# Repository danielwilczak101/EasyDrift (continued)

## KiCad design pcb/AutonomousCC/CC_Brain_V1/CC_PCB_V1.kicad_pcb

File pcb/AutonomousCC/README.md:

# AutonomousCC

PCB Design Version 1

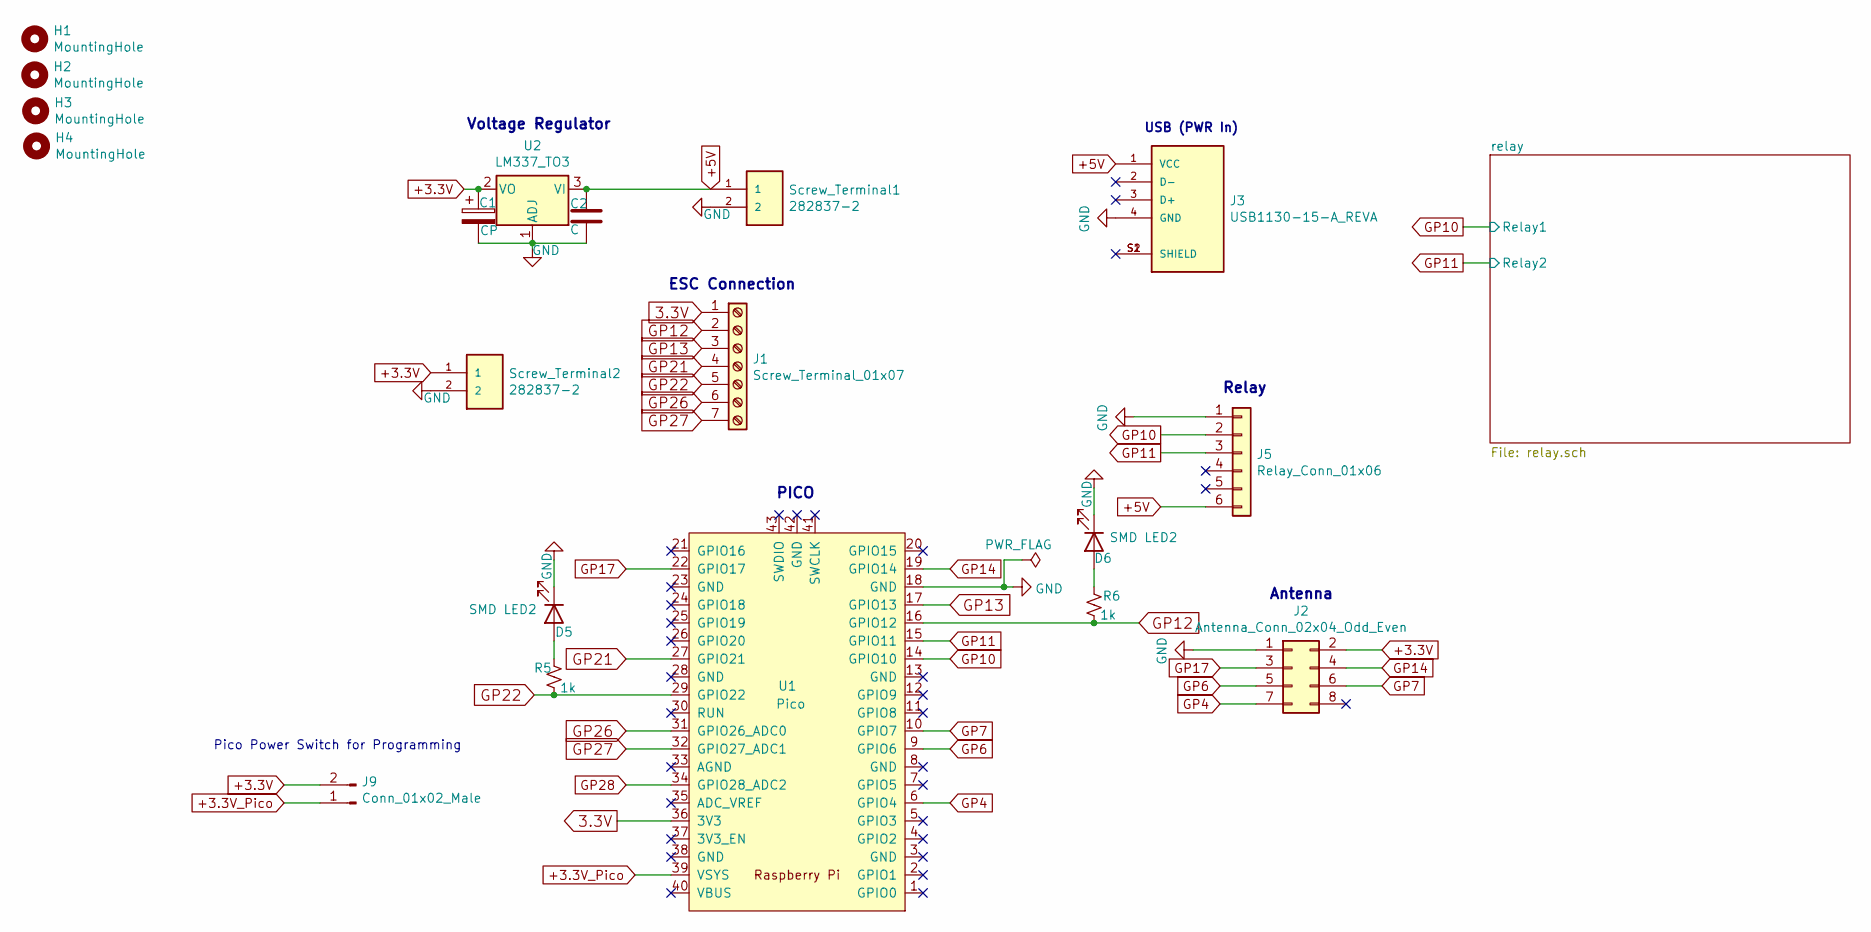
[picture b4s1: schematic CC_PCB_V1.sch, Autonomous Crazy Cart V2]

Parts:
C1: CP; CP_Radial_D4.0mm_P1.50mm
C2: C; CP_Radial_D4.0mm_P1.50mm
D5, D6: SMD LED2; LED_1206_3216Metric_Pad1.42x1.75mm_HandSolder
H1, H2, H3, H4: MountingHole; MountingHole_3mm
J1: Screw_Terminal_01x07; TerminalBlock_TE_282834-7_1x07_P2.54mm_Horizontal
J2: Antenna_Conn_02x04_Odd_Even; PinHeader_2x04_P2.54mm_Vertical
J3: USB1130-15-A_REVA; GCT_USB1130-15-A_REVA; PARTREV A
J5: Relay_Conn_01x06; PinHeader_1x06_P2.54mm_Vertical
J9: Conn_01x02_Male; PinHeader_1x02_P2.54mm_Vertical
R5, R6: 1k; R_0603_1608Metric_Pad0.98x0.95mm_HandSolder
Screw_Terminal1, Screw_Terminal2: 282837-2; TE_282837-2
U1: Pico; RPi_Pico_SMD_TH
U2: LM337_TO3; SOT230P696X180-4N

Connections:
3.3V: J1.1, U1.36 (3V3)
+3.3V: C1.1, J2.2, J9.2, Screw_Terminal2.1, U2.2 (VO)
+3.3V_Pico: J9.1, U1.39 (VSYS)
+5V: C2.1, J3.1 (VCC), J5.6, Screw_Terminal1.1, U2.3 (VI); also elsewhere on the board
GND: C1.2, C2.2, D5.1 (K), D6.1 (K), J2.1, J3.4 (GND), J5.1, Screw_Terminal1.2, Screw_Terminal2.2, U1.18 (GND), U2.1 (ADJ); also elsewhere on the board
GP4: J2.7, U1.6 (GPIO4)
GP6: J2.5, U1.9 (GPIO6)
GP7: J2.6, U1.10 (GPIO7)
GP10: J5.2, U1.14 (GPIO10); also elsewhere on the board
GP11: J5.3, U1.15 (GPIO11); also elsewhere on the board
GP12: J1.2, R6.2, U1.16 (GPIO12)
GP13: J1.3, U1.17 (GPIO13)
GP14: J2.4, U1.19 (GPIO14)
GP17: J2.3, U1.22 (GPIO17)
GP21: J1.4, U1.27 (GPIO21)
GP22: J1.5, R5.2, U1.29 (GPIO22)
GP26: J1.6, U1.31 (GPIO26_ADC0)
GP27: J1.7, U1.32 (GPIO27_ADC1)
GP28: U1.34 (GPIO28_ADC2)
unnamed: D5.2 (A), R5.1
unnamed: D6.2 (A), R6.1
unnamed: J3.S1 (SHIELD), J3.S2 (SHIELD)

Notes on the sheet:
Antenna
Relay
PICO
ESC Connection
Voltage Regulator
Pico Power Switch for Programming
USB (PWR In)

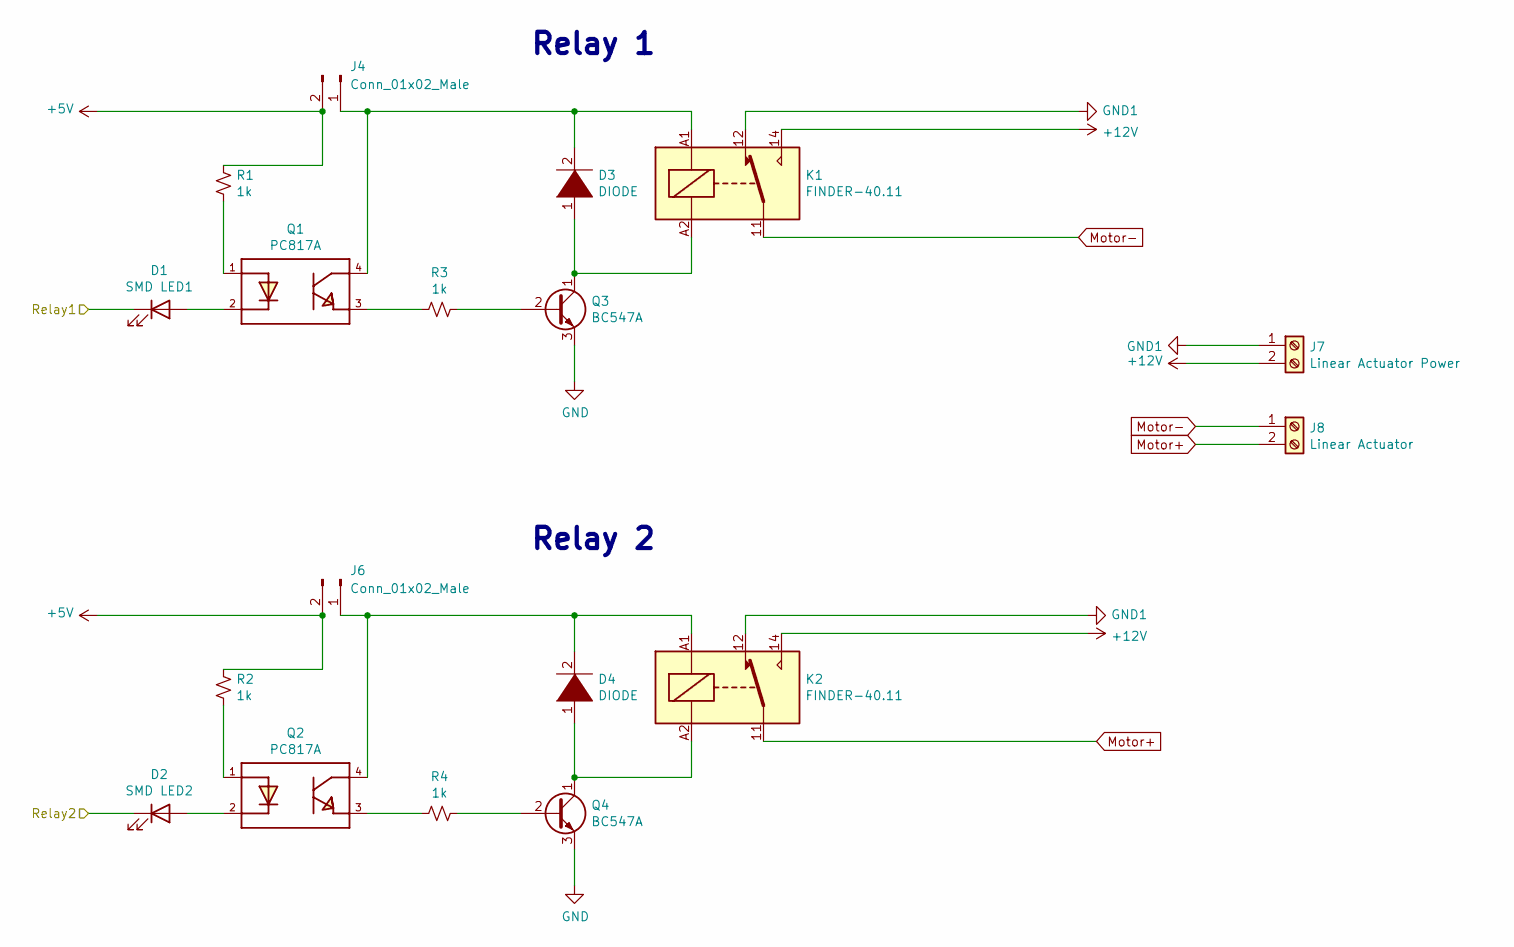
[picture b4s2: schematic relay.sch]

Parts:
D1: SMD LED1; LED_1206_3216Metric_Pad1.42x1.75mm_HandSolder
D2: SMD LED2; LED_1206_3216Metric_Pad1.42x1.75mm_HandSolder
D3, D4: DIODE; D_1210_3225Metric_Pad1.42x2.65mm_HandSolder
J4, J6: Conn_01x02_Male; PinHeader_1x02_P2.54mm_Vertical
J7: Linear Actuator Power; TE_282837-2
J8: Linear Actuator; TE_282837-2
K1, K2: FINDER-40.11; Relay_SPDT_Finder_36.11
Q1, Q2: PC817A; DIP762W50P254L650H458Q4B
Q3, Q4: BC547A; TO-92_Inline
R1, R2, R3, R4: 1k; R_0603_1608Metric_Pad0.98x0.95mm_HandSolder

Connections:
+5V: J4.2, J6.2, R1.1, R2.1; also elsewhere on the board
+12V: J7.2, K1.14, K2.14
GND: Q3.3 (E), Q4.3 (E); also elsewhere on the board
GND1: J7.1, K1.12, K2.12
GP10: D1.1 (K); also elsewhere on the board
GP11: D2.1 (K); also elsewhere on the board
Motor+: J8.2, K2.11
Motor-: J8.1, K1.11
unnamed: D1.2 (A), Q1.2
unnamed: D2.2 (A), Q2.2
unnamed: D3.1 (K), K1.A2, Q3.1 (C)
unnamed: D3.2 (A), J4.1, K1.A1, Q1.4
unnamed: D4.1 (K), K2.A2, Q4.1 (C)
unnamed: D4.2 (A), J6.1, K2.A1, Q2.4
unnamed: Q1.1, R1.2
unnamed: Q1.3, R3.2
unnamed: Q2.1, R2.2
unnamed: Q2.3, R4.2
unnamed: Q3.2 (B), R3.1
unnamed: Q4.2 (B), R4.1

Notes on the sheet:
Relay 1
Relay 2

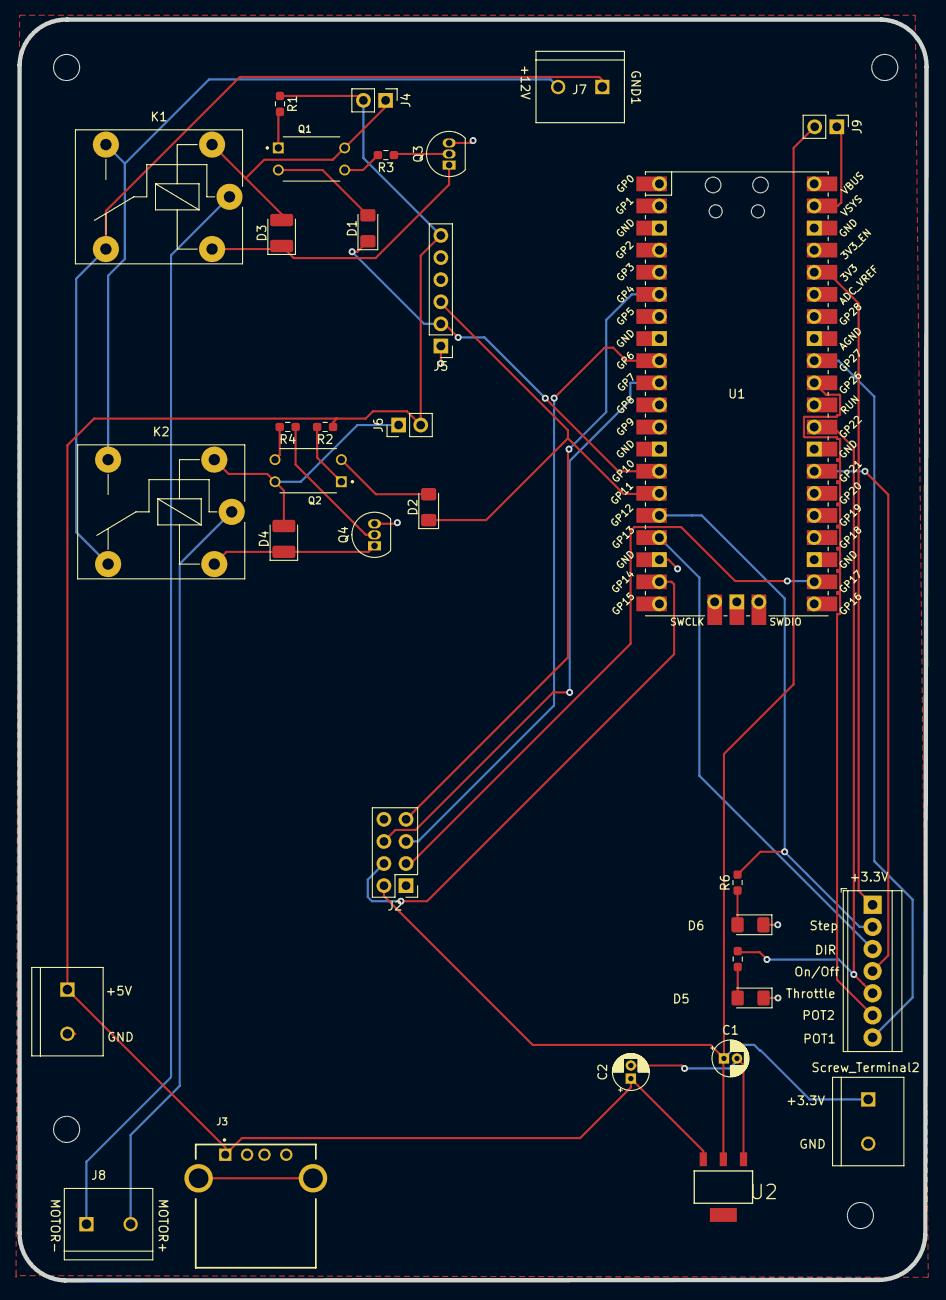
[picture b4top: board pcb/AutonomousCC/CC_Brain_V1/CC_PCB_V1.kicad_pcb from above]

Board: 2 copper layers, 104.2 x 144.9 mm, 37 parts (0 on the bottom side), 37 nets.

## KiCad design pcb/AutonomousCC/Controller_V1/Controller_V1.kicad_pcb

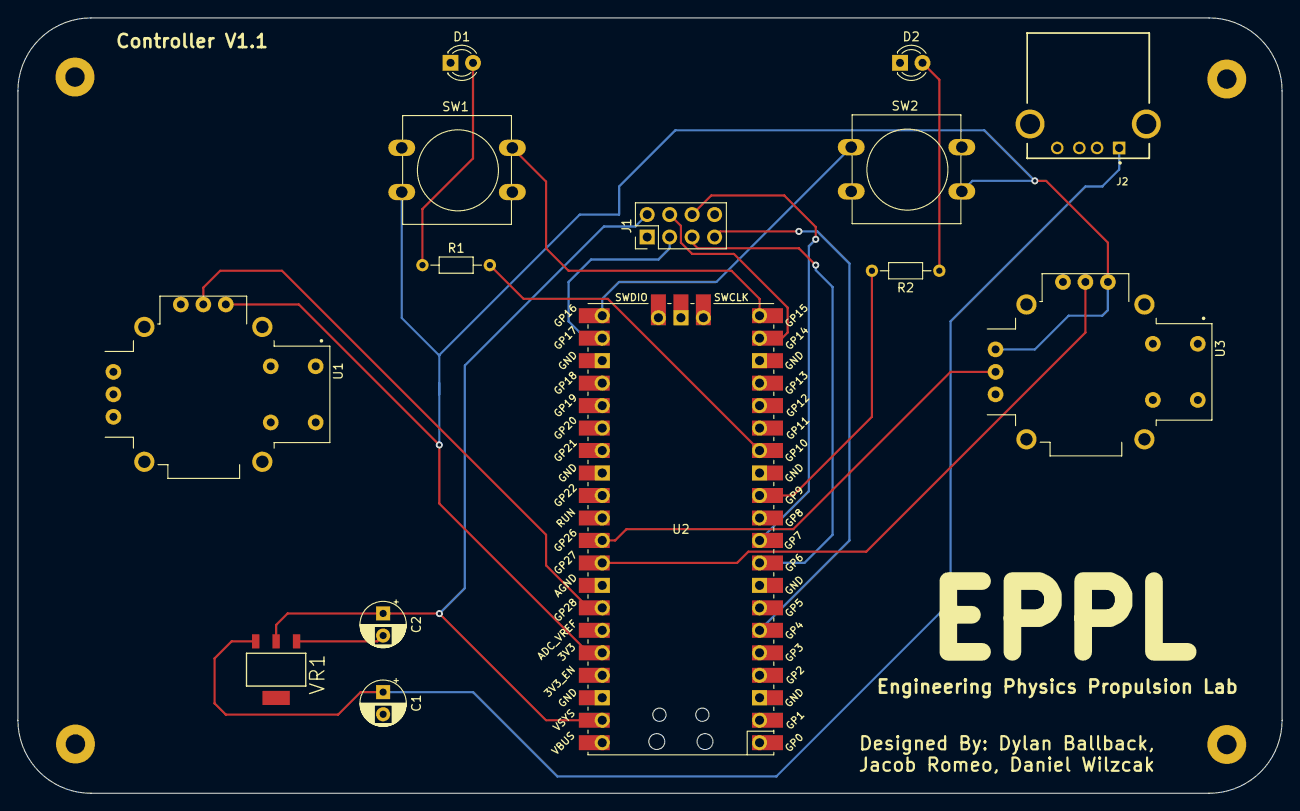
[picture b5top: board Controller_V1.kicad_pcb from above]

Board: 2 copper layers, 142.9 x 87.6 mm, 18 parts (0 on the bottom side), 21 nets.

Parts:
C1: C_Small; CP_Radial_D5.0mm_P2.50mm
C2: CP1; CP_Radial_D5.0mm_P2.50mm
D1: Green_LED; LED_D3.0mm
D2: RED_LED; LED_D3.0mm
H4: MountingHole; MountingHole_2.2mm_M2_Pad
He: MountingHole; MountingHole_2.2mm_M2_Pad
He#2: MountingHole; MountingHole_2.2mm_M2_Pad
J1: Antenna_Conn_02x04_Odd_Even; PinHeader_2x04_P2.54mm_Vertical
J2: USB1130-15-A_REVA; GCT_USB1130-15-A_REVA
R1, R2: 220_R_Small_US; R_Axial_DIN0204_L3.6mm_D1.6mm_P7.62mm_Horizontal
SW1, SW2: SW_12mm_Push; SW_PUSH-12mm
U1, U3: COM-09032; XDCR_COM-09032
U2: Pico; RPi_Pico_SMD_TH
VR1: LM1117T-3.3_NOPB; SOT230P696X180-4N
e: MountingHole; MountingHole_2.2mm_M2_Pad

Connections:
+3.3VA: C2.1, J1.2, U2.39, VR1.2
+3V3: SW1.2, SW2.2, U1.V1, U2.36, U3.H1, U3.V1
+5V: C1.1, J2.1, VR1.3
GND: C1.2, C2.2, D1.1, D2.1, J1.1, J2.4, U1.V3, U2.38, U3.H3, U3.V3, VR1.1
GP04: J1.7, U2.6
GP06: J1.5, U2.9
GP07: J1.6, U2.10
GP09: R2.2, U2.12
GP10: R1.2, U2.14
GP14: J1.4, U2.19
GP15: SW1.1, U2.20
GP16: SW2.1, U2.21
GP17: J1.3, U2.22
GP26: U2.31, U3.H2
GP27: U2.32, U3.V2
GP28: U1.V2, U2.34
unnamed: D1.2, R1.1
unnamed: D2.2, R2.1
unnamed: J2.S1, J2.S2
unnamed: U1.S1, U1.S2, U1.S3, U1.S4
unnamed: U3.S1, U3.S2, U3.S3, U3.S4

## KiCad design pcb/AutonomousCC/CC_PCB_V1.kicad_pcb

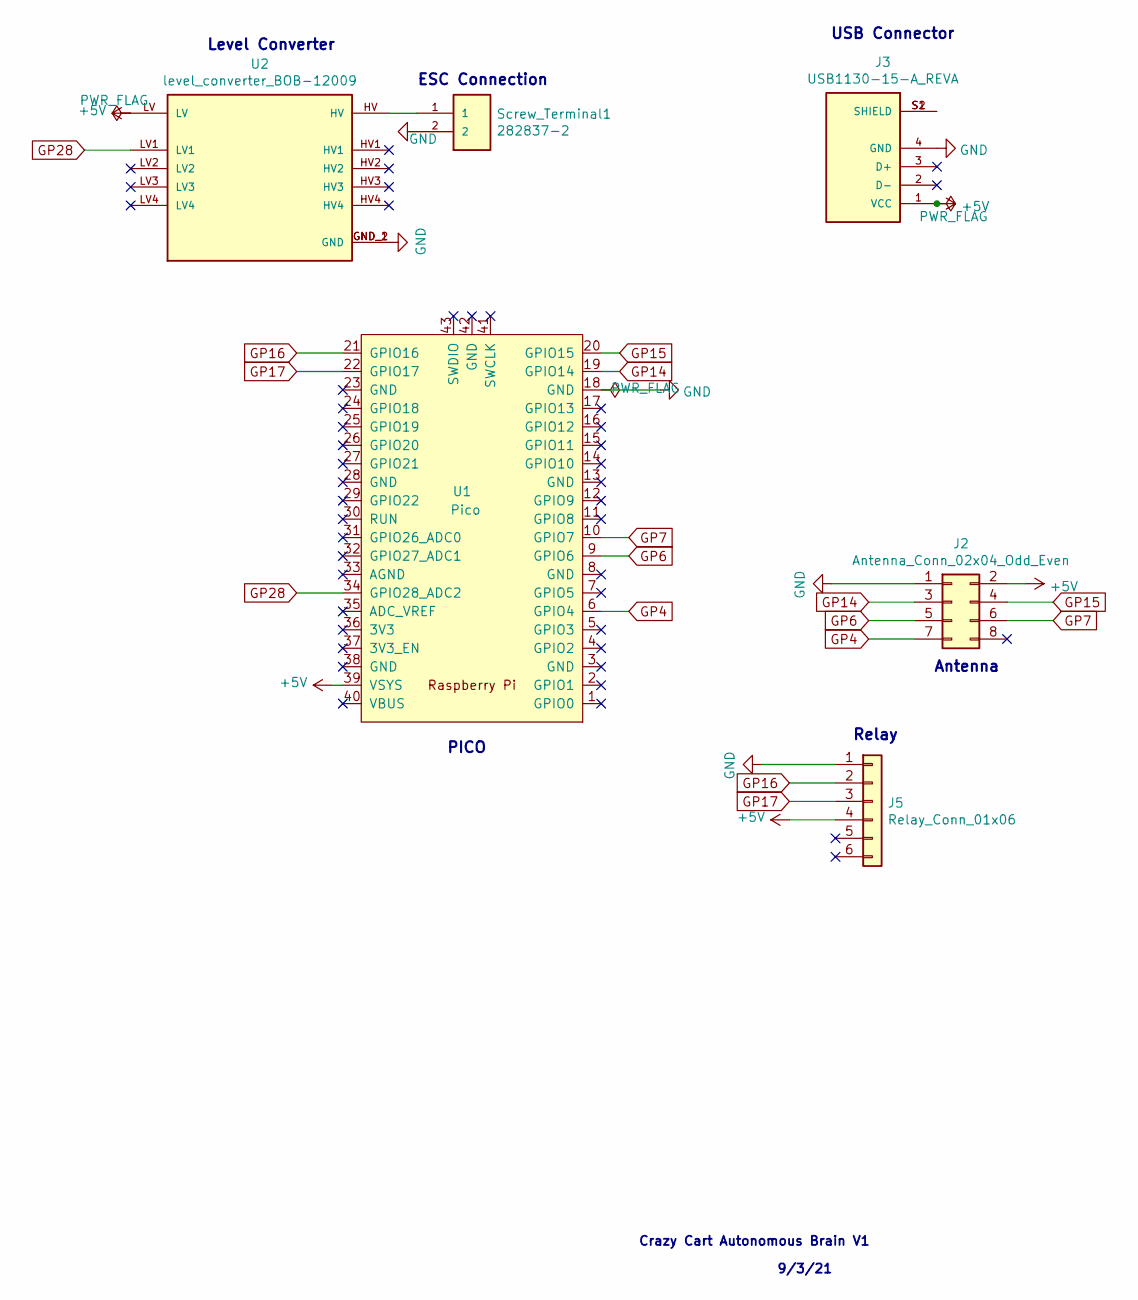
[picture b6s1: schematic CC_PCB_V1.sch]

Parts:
J2: Antenna_Conn_02x04_Odd_Even; PinHeader_2x04_P2.00mm_Vertical
J3: USB1130-15-A_REVA; GCT_USB1130-15-A_REVA; PARTREV A
J5: Relay_Conn_01x06; PinHeader_1x06_P2.00mm_Vertical
Screw_Terminal1: 282837-2; TE_282837-2
U1: Pico; RPi_Pico_SMD_TH
U2: level_converter_BOB-12009; CONV_BOB-12009; PARTREV 01

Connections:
+5V: J2.2, J3.1 (VCC), J5.4, U1.39 (VSYS), U2.LV
GND: J2.1, J3.4 (GND), J5.1, Screw_Terminal1.2, U1.18 (GND), U2.GND_1 (GND), U2.GND_2 (GND)
GP4: J2.7, U1.6 (GPIO4)
GP6: J2.5, U1.9 (GPIO6)
GP7: J2.6, U1.10 (GPIO7)
GP14: J2.3, U1.19 (GPIO14)
GP15: J2.4, U1.20 (GPIO15)
GP16: J5.2, U1.21 (GPIO16)
GP17: J5.3, U1.22 (GPIO17)
GP28: U1.34 (GPIO28_ADC2), U2.LV1
unnamed: J3.S1 (SHIELD), J3.S2 (SHIELD)
unnamed: Screw_Terminal1.1, U2.HV

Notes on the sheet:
9/3/21
Crazy Cart Autonomous Brain V1
Antenna
Relay
PICO
Level Converter
USB Connector
ESC Connection

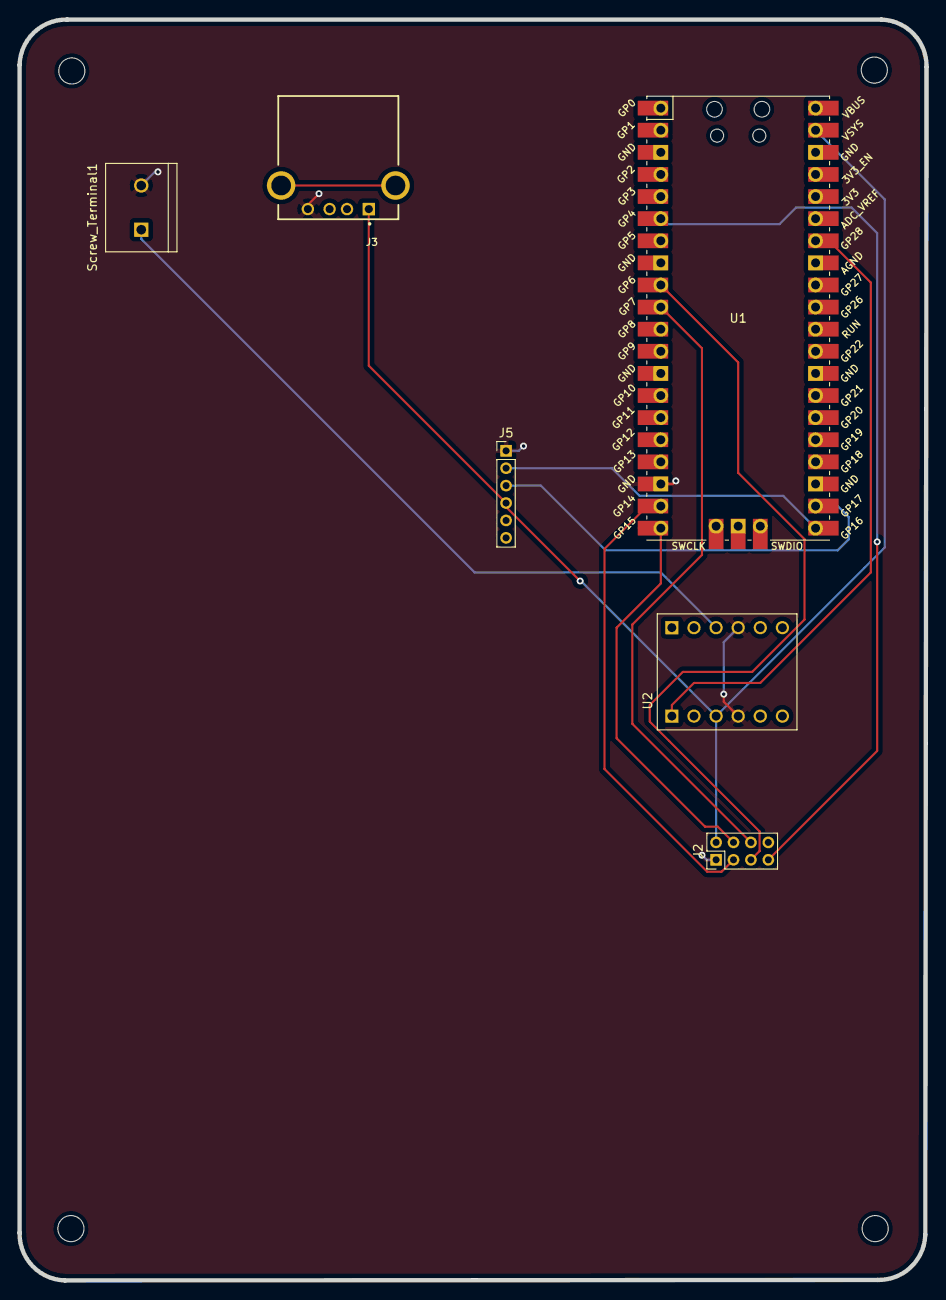
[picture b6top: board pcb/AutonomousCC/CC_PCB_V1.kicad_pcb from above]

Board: 2 copper layers, 104.2 x 144.9 mm, 6 parts (0 on the bottom side), 12 nets.

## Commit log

2020-10-20 Added comments to the code
2020-11-17 Added 3d print folder
2021-08-30 Basiclly first commit.
2021-08-30 Removed unneeded files.
2021-08-30 Initial commit for reciever
2021-08-31 Added throttle functionality.
2021-09-04 Folder restructure
2021-09-06 new design
2021-09-06 Figured out throttle + direction on transmit
2021-09-06 Pushed recieve data comments
2021-09-07 Added main functionality.
2021-09-07 Transmit functional changes
2021-09-07 Creating New file to store all the PCB changes
2021-09-07 JK created file not folder
2021-09-07 Uploading the V1 PCB for Autonomous Cart
2021-09-07 I spelled autonomous wrong hehe
2021-09-24 Controller Design
2021-09-25 Added USB Port, Button, LED
2021-09-26 Updated Sch
2021-09-26 Updated pcb footprints
2021-09-26 Autosave
2021-09-27 Updated PCB Layout
2021-09-27 Updated REF Visibility
2021-09-27 Updated Tracing
2021-09-27 Updated Ground Layer
2021-09-27 Update Silk Mask
2021-09-27 Created Gerber Files
2021-10-01 removing to update.
2021-10-01 update CC_Brain_V1 PCB
2021-10-01 Update To Correct Footprint Sizes
2021-10-04 Added Switch for Pico Programming
2021-10-06 Update Controller Antenna Pins
2021-10-06 Updated Antenna CC_Brain Pins and Added Relay Circuit
2021-10-08 Added Header Pin Connector
2021-10-09 Moved to working version..
2021-10-09 Added most of the footprints
    Still need Diodes, Resistors (if THT or SMD), and LED footprints
2021-10-09 Updated Footprints and PCB Layout
2021-10-10 Updated Footprint and Fixed PCB Layout
2021-10-11 Finished PCB tracing
2021-10-13 OK, OK now we are done
2021-10-14 Saved Gerber Files
2021-10-16 CC Controller and Brain VERSION 1.1
2022-05-04 Added drivable camera code.
2022-06-28 Finished tracing the Linear Actuator
2022-07-01 Deleted old folder
2022-07-01 refreshed linear actuator pcb
2022-07-12 Traced Stepper Motor PCB
2022-08-05 Made PCB smaller
2022-08-06 update pcb
2022-09-12 Finished Traces
2022-09-19 Uploaded Gerber
2024-02-05 New RC control PCB for dirft cart
